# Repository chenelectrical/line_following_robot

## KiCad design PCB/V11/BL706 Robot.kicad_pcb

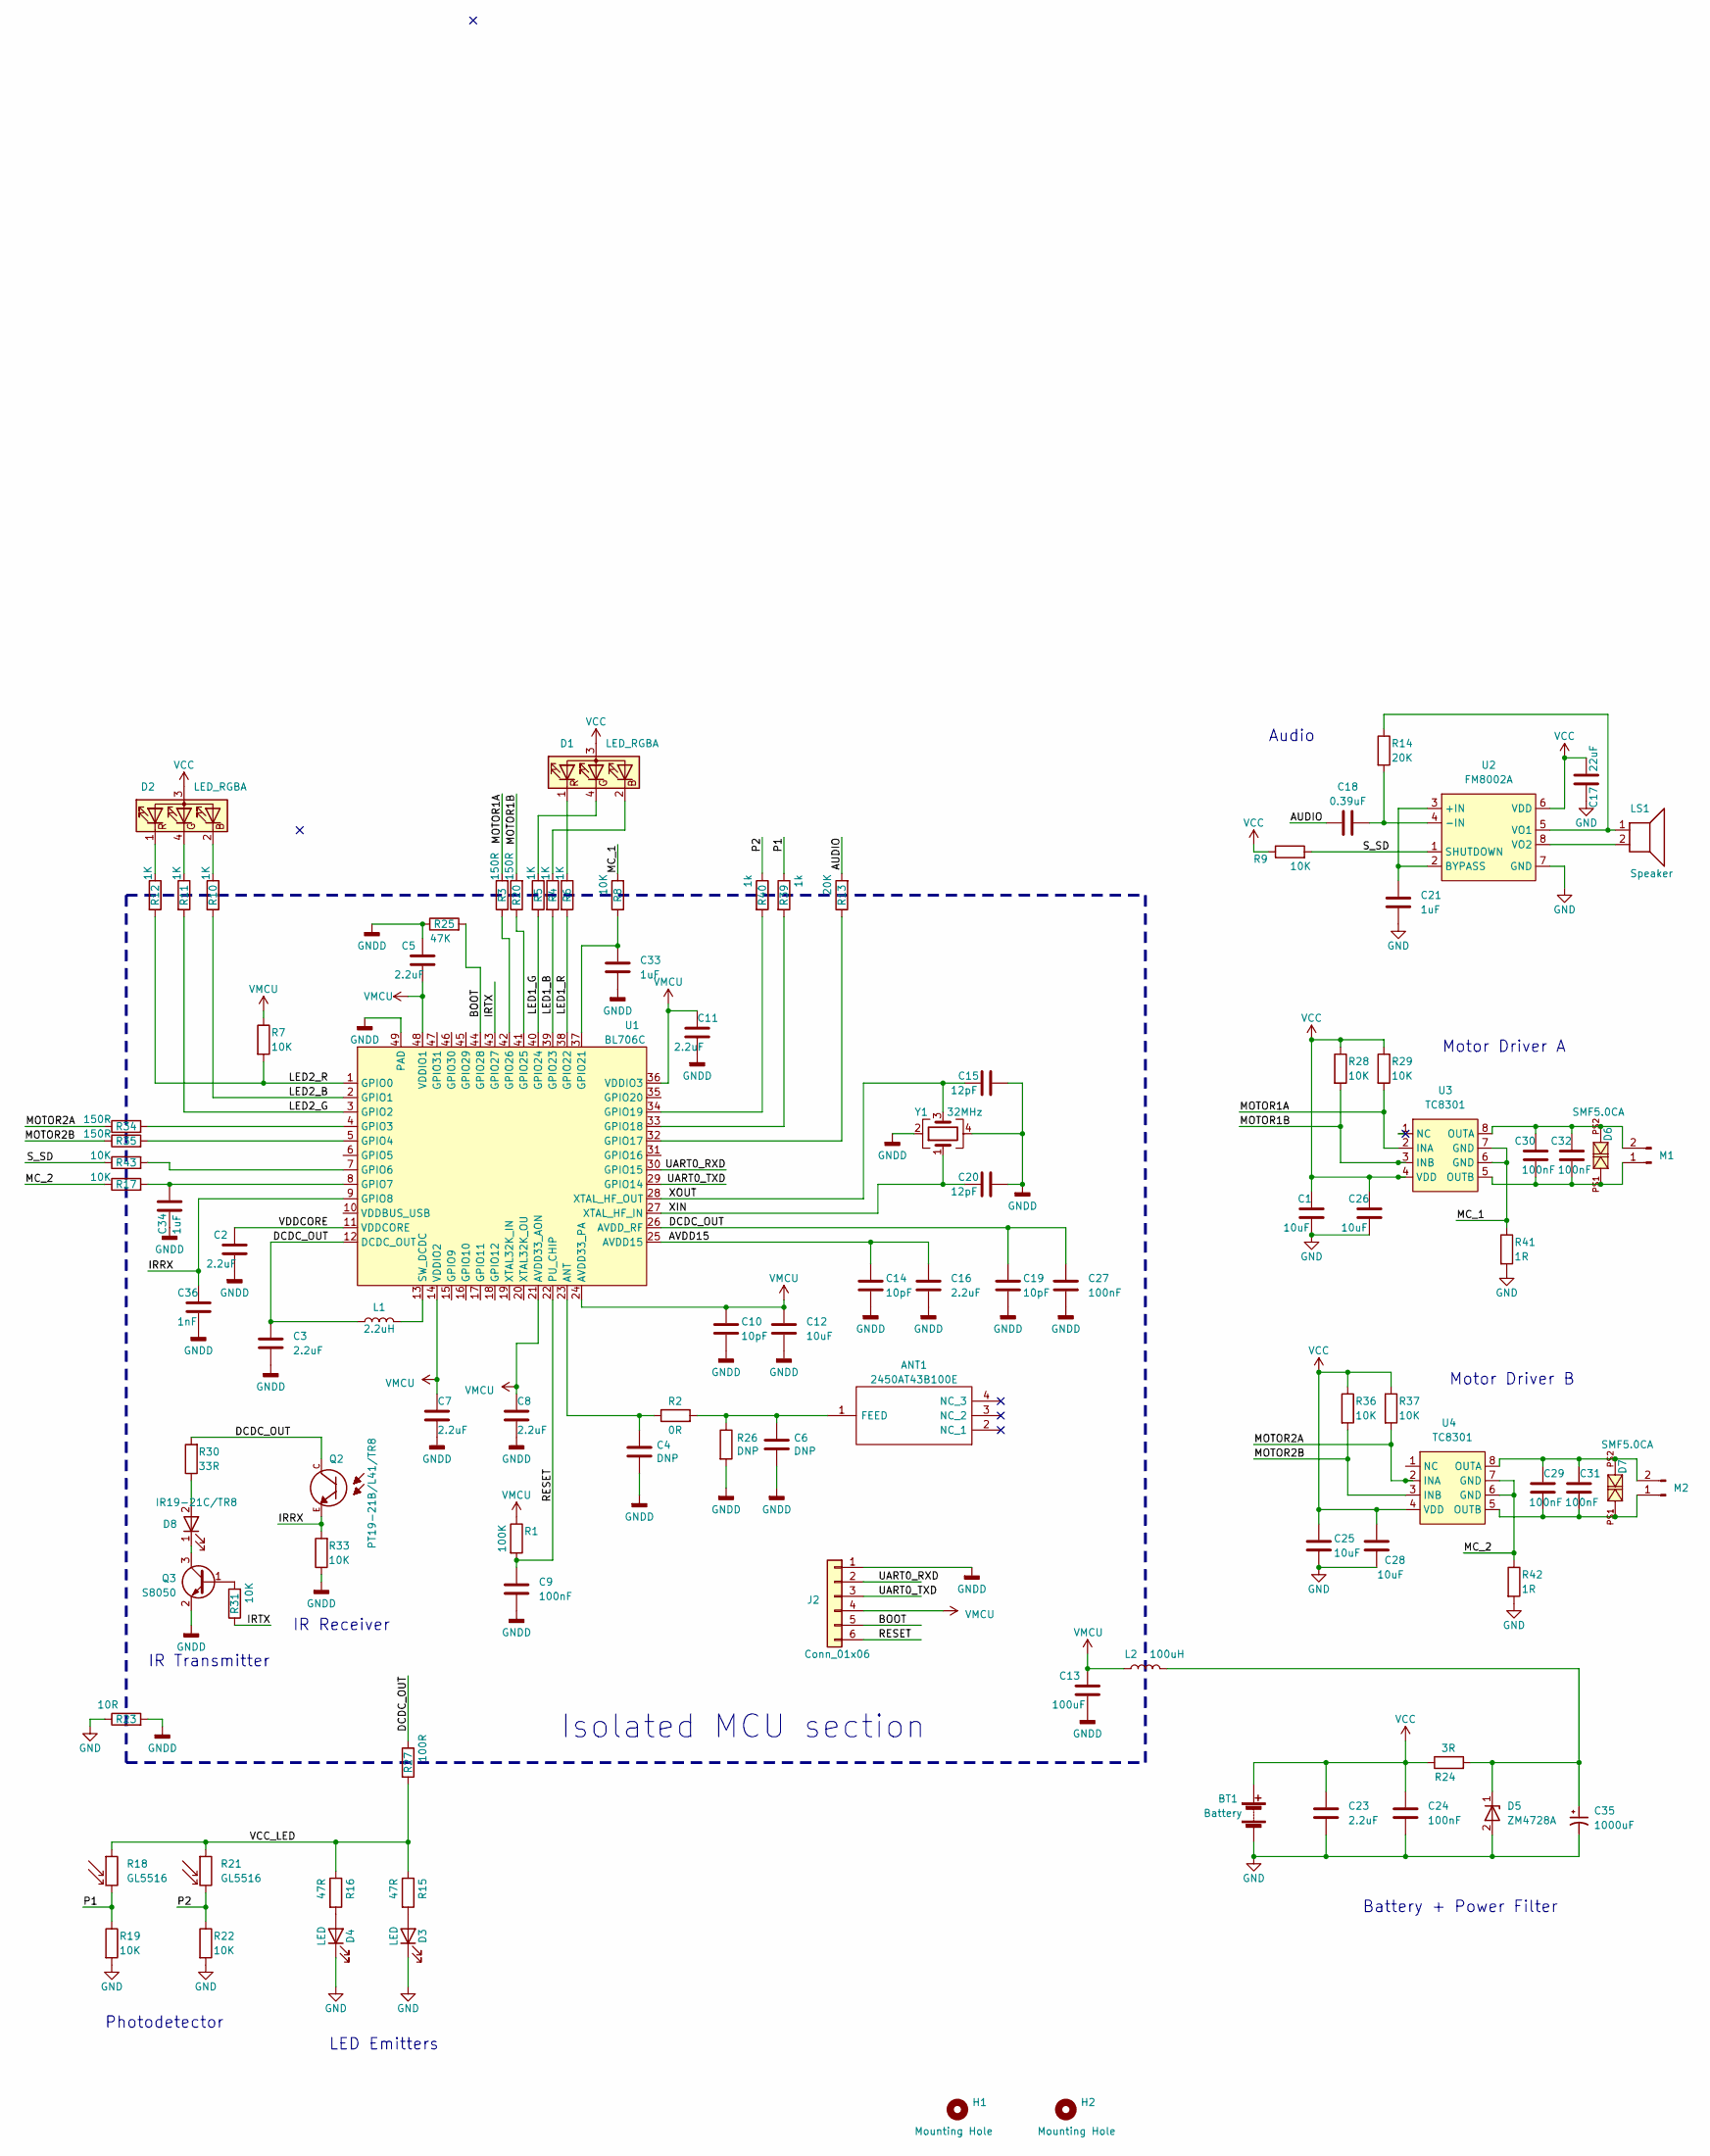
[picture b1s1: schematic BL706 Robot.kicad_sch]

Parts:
ANT1: 2450AT43B100E; LCSC C2917721
BT1: Battery; JST_PH_B2B-PH-K_1x02_P2.00mm_Vertical; LCSC C131337
C1, C12, C25, C26, C28: 10uF; C_0603_1608Metric; LCSC C96446
C2, C3, C5, C7, C8, C11, C16, C23: 2.2uF; C_0402_1005Metric; LCSC C12530
C4, C6: DNP; C_0402_1005Metric
C9, C24, C27, C29, C30, C31, C32: 100nF; C_0402_1005Metric; LCSC C307331
C10, C14, C19: 10pF; C_0402_1005Metric; LCSC C32949
C13: 100uF; CP_EIA-3528-21_Kemet-B; LCSC C129567
C15, C20: 12pF; C_0402_1005Metric; LCSC C1547
C17: 22uF; C_0603_1608Metric; LCSC C162690
C18: 0.39uF; C_0603_1608Metric; LCSC C309480
C21: 1uF; C_0603_1608Metric; LCSC C105504
C33, C34: 1uF; C_0402_1005Metric; LCSC C52923
C35: 1000uF; CP_Elec_8x10.5; LCSC C99833
C36: 1nF; C_0402_1005Metric; LCSC C141053
D1, D2: LED_RGBA; FM-B2020RGBA-HG; LCSC C108793
D3, D4: LED; LED_D3.0mm_Horizontal_O1.27mm_Z2.0mm
D5: ZM4728A; D_MELF; LCSC C38989
D6, D7: SMF5.0CA; SOD-123FL; LCSC C320548
D8: IR19-21C/TR8; IR19-21C-TR8; LCSC C142316
H1, H2: Mounting Hole; MountingHole_3mm
J2: Conn_01x06; PinHeader_1x06_P1.27mm_Vertical
L1: 2.2uH; L_0805_2012Metric; LCSC C86089
L2: 100uH; L_0805_2012Metric; LCSC C223180
LS1: Speaker; JST_XH_B2B-XH-A_1x02_P2.50mm_Vertical; LCSC C158012
M1, M2: Conn_01x02_Male; JST_XH_B2B-XH-A_1x02_P2.50mm_Vertical; LCSC C158012
Q2: PT19-21B/L41/TR8; XDCR_PT19-21B_L41_TR8; LCSC C131258
Q3: S8050; SOT-23-3; LCSC C2926165
R1: 100K; R_0402_1005Metric; LCSC C208776
R2: 0R; R_0402_1005Metric; LCSC C102745
R3, R20, R34, R35: 150R; R_0402_1005Metric; LCSC C140202
R4, R5, R6, R10, R11, R12: 1K; R_0402_1005Metric; LCSC C11702
R7, R8, R9, R17, R19, R22, R28, R29, R31, R33, R43: 10K; R_0402_1005Metric; LCSC C25744
R13, R14: 20K; R_0402_1005Metric; LCSC C25765
R15, R16: 47R; R_0402_1005Metric; LCSC C284589
R18, R21: GL5516; R_LDR_5.0x4.1mm_P3mm_Vertical
R23: 10R; R_1206_3216Metric; LCSC C326706
R24: 3R; R_1206_3216Metric; LCSC C3152278
R25: 47K; R_0402_1005Metric; LCSC C163830
R26: DNP; R_0402_1005Metric
R27: 100R; R_0805_2012Metric; LCSC C2907218
R30: 33R; R_0402_1005Metric; LCSC C208868
R36, R37: 10K; R_0402_1005Metric; LCSC PN C25744
R39, R40: 1k; R_0402_1005Metric; LCSC C11702
R41, R42: 1R; R_1206_3216Metric; LCSC C17928
U1: BL706C; QFN-48-1EP_6x6mm_P0.4mm_EP4.3x4.3mm; LCSC C2874060
U2: FM8002A; SOP-8_3.9x4.9mm_P1.27mm; LCSC C94625
U3, U4: TC8301; SOP-8_3.9x4.9mm_P1.27mm; LCSC C2887481
Y1: 32MHz; Crystal_SMD_2016-4Pin_2.0x1.6mm; LCSC C255896

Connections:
/AUDIO: C18.1, R13.2
/AVDD15: C14.1, C16.1, U1.25 (AVDD15)
/BOOT: J2.5, R25.2, U1.44 (GPIO28)
/DCDC_OUT: C3.1, C19.1, C27.1, L1.1, Q2.C, R27.1, R30.2, U1.12 (DCDC_OUT), U1.26 (AVDD_RF)
/IRRX: C36.1, Q2.E, R33.2, U1.9 (GPIO8)
/IRTX: R31.1, U1.43 (GPIO27)
/LED1_B: R4.2, U1.39 (GPIO23)
/LED1_G: R5.2, U1.40 (GPIO24)
/LED1_R: R6.2, U1.38 (GPIO22)
/LED2_B: R10.2, U1.2 (GPIO1)
/LED2_G: R11.2, U1.3 (GPIO2)
/LED2_R: R7.2, R12.2, U1.1 (GPIO0)
/MC_1: R8.2, R41.1, U3.6 (GND), U3.7 (GND)
/MC_2: R17.1, R42.1, U4.6 (GND), U4.7 (GND)
/MOTOR1A: R3.2, R29.2, U3.2 (INA)
/MOTOR1B: R20.2, R28.2, U3.3 (INB)
/MOTOR2A: R34.1, R37.2, U4.2 (INA)
/MOTOR2B: R35.1, R36.2, U4.3 (INB)
/P1: R18.2, R19.1, R39.1
/P2: R21.2, R22.1, R40.1
/RESET: C9.1, J2.6, R1.2, U1.22 (PU_CHIP)
/S_SD: R9.2, R43.1, U2.1 (SHUTDOWN)
/UART0_RXD: J2.2, U1.30 (GPIO15)
/UART0_TXD: J2.3, U1.29 (GPIO14)
/VCC_LED: R15.1, R16.1, R18.1, R21.1, R27.2
/VDDCORE: C2.1, U1.11 (VDDCORE)
/XIN: C20.2, U1.27 (XTAL_HF_IN), Y1.1
/XOUT: C15.2, U1.28 (XTAL_HF_OUT), Y1.3
GND: BT1.2 (-), C1.2, C17.2, C21.2, C23.2, C24.2, C25.2, C26.2, C28.2, C35.2, D3.1 (K), D4.1 (K), D5.2 (A), R19.2, R22.2, R23.1, R41.2, R42.2, U2.7 (GND)
GNDD: C2.2, C3.2, C4.2, C5.1, C6.2, C7.2, C8.2, C9.2, C10.2, C11.1, C12.2, C13.2, C14.2, C15.1, C16.2, C19.2, C20.1, C27.2, C33.2, C34.2, C36.2, J2.1, Q3.2 (E), R23.2, R25.1, R26.2, R33.1, U1.49 (PAD), Y1.2, Y1.4
unnamed: ANT1.1 (FEED), C6.1, R2.2, R26.1
unnamed: D1.2 (BK), R4.1
unnamed: D1.4 (GK), R5.1
unnamed: D1.1 (RK), R6.1
unnamed: D2.2 (BK), R10.1
unnamed: D2.4 (GK), R11.1
unnamed: D2.1 (RK), R12.1
unnamed: D3.2 (A), R15.2
unnamed: D4.2 (A), R16.2
unnamed: C35.1, D5.1 (K), L2.2, R24.2
unnamed: D8.2 (A), R30.1
unnamed: D8.1 (K), Q3.3 (C)
unnamed: C30.2, C32.2, D6.P$1, M1.1, U3.5 (OUTB)
unnamed: C30.1, C32.1, D6.P$2, M1.2, U3.8 (OUTA)
unnamed: C29.2, C31.2, D7.P$1, M2.1, U4.5 (OUTB)
unnamed: C29.1, C31.1, D7.P$2, M2.2, U4.8 (OUTA)
unnamed: Q3.1 (B), R31.2
unnamed: C4.1, R2.1, U1.23 (ANT)
unnamed: R34.2, U1.4 (GPIO3)
unnamed: R35.2, U1.5 (GPIO4)
unnamed: R43.2, U1.7 (GPIO6)
unnamed: C34.1, R17.2, U1.8 (GPIO7)
unnamed: R13.1, U1.32 (GPIO17)
unnamed: R39.2, U1.33 (GPIO18)
unnamed: R40.2, U1.34 (GPIO19)
unnamed: C33.1, R8.1, U1.37 (GPIO21)
unnamed: R20.1, U1.41 (GPIO25)
unnamed: R3.1, U1.42 (GPIO26)
unnamed: L1.2, U1.13 (SW_DCDC)
unnamed: C21.1, U2.2 (BYPASS), U2.3 (+IN)
unnamed: C18.2, R14.2, U2.4 (-IN)
unnamed: LS1.1, R14.1, U2.5 (VO1)
unnamed: LS1.2, U2.8 (VO2)
VCC: BT1.1 (+), C1.1, C17.1, C23.1, C24.1, C25.1, C26.1, C28.1, D1.3 (A), D2.3 (A), R9.1, R24.1, R28.1, R29.1, R36.1, R37.1, U2.6 (VDD), U3.4 (VDD), U4.4 (VDD)
VPP: C5.2, C7.1, C8.1, C10.1, C11.2, C12.1, C13.1, J2.4, L2.1, R1.1, R7.1, U1.14 (VDDIO2), U1.21 (AVDD33_AON), U1.24 (AVDD33_PA), U1.36 (VDDIO3), U1.48 (VDDIO1)

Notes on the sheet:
Photodetector
Audio
LED Emitters
Motor Driver A
Battery + Power Filter
Isolated MCU section
IR Transmitter
Motor Driver B
IR Receiver

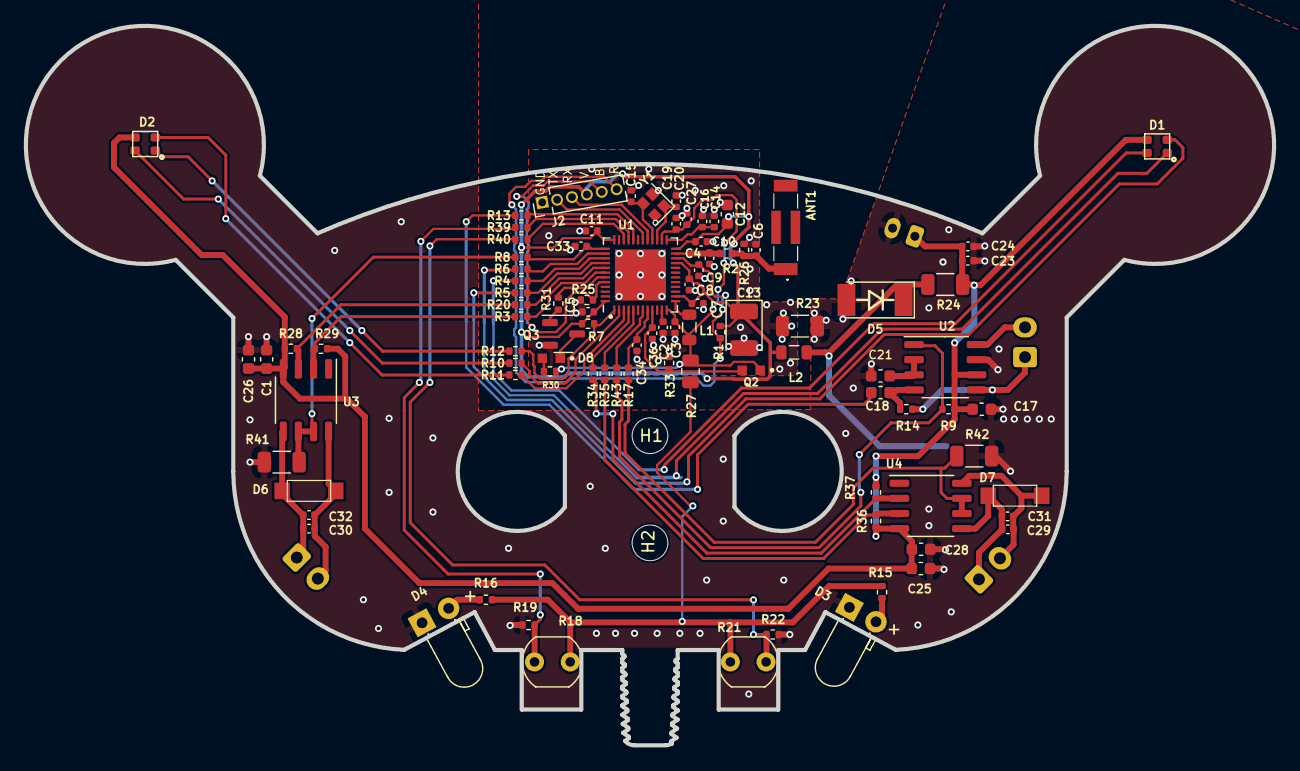
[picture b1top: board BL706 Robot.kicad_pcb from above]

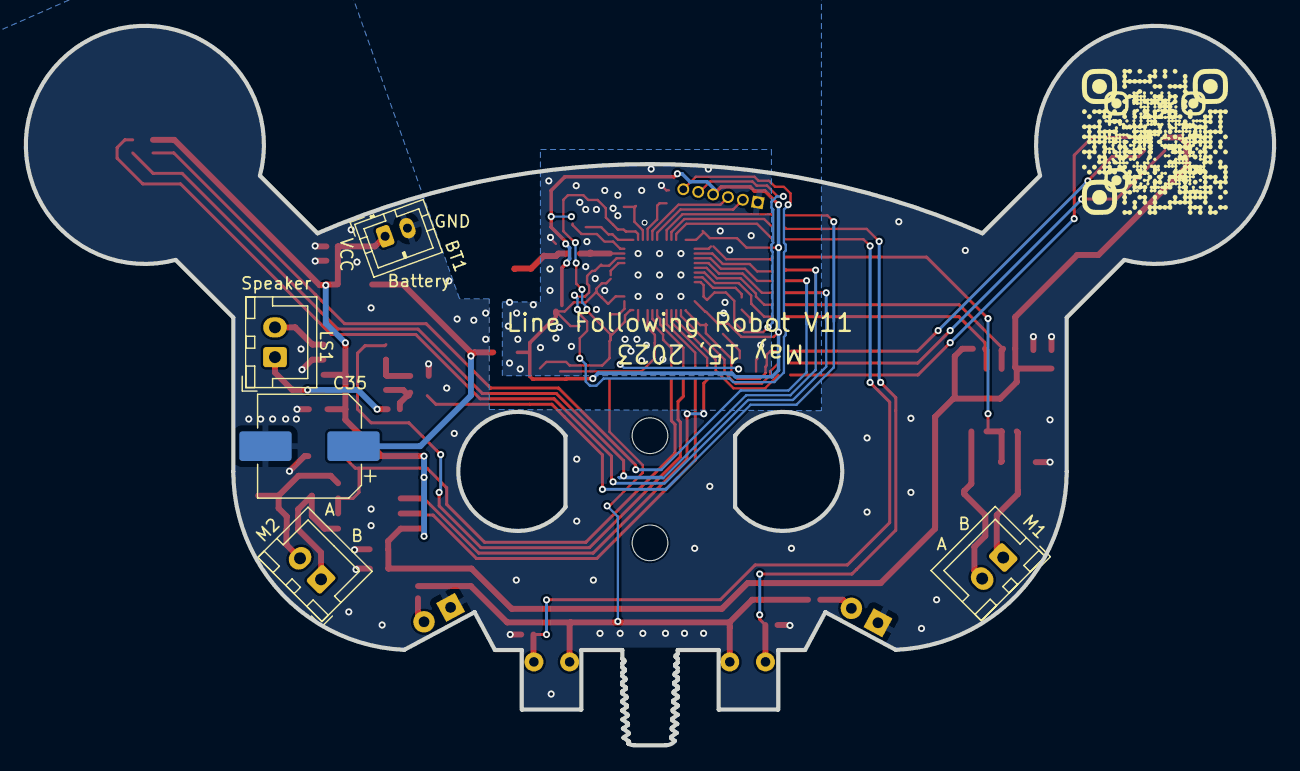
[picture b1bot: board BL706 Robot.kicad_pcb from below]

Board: 2 copper layers, 104.8 x 60.4 mm, 101 parts (5 on the bottom side), 65 nets.

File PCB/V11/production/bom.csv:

Designator,Footprint,Quantity,Value,LCSC Part #
ANT1,2450AT43B100E,1,2450AT43B100E,C2917721
BT1,JST_PH_B2B-PH-K_1x02_P2.00mm_Vertical,1,Battery,C131337
"C1, C12, C25, C26, C28",0603,5,10uF,C96446
"C10, C14, C19",0402,3,10pF,C32949
"C11, C16, C2, C23, C3, C5, C7, C8",0402,8,2.2uF,C12530
C13,CP_EIA-3528-21_Kemet-B,1,100uF,C129567
"C15, C20",0402,2,12pF,C1547
C17,0603,1,22uF,C162690
C18,0603,1,0.39uF,C309480
C21,0603,1,1uF,C105504
"C24, C27, C29, C30, C31, C32, C9",0402,7,100nF,C307331
"C33, C34",0402,2,1uF,C52923
C35,CP_Elec_8x10.5,1,1000uF,C99833
C36,0402,1,1nF,C141053
"C4, C6, R26",0402,3,DNP,
"D1, D2",FM-B2020RGBA-HG,2,LED_RGBA,C108793
"D3, D4",LED_D3.0mm_Horizontal_O1.27mm_Z2.0mm,2,LED,
D5,D_MELF,1,ZM4728A,C38989
"D6, D7",SOD-123FL,2,SMF5.0CA,C320548
D8,IR19-21C-TR8,1,IR19-21C/TR8,C142316
"H1, H2",MountingHole_3mm,2,Mounting Hole,
J2,PinHeader_1x06_P1.27mm_Vertical,1,Conn_01x06,
L1,0805,1,2.2uH,C86089
L2,0805,1,100uH,C223180
LS1,JST_XH_B2B-XH-A_1x02_P2.50mm_Vertical,1,Speaker,C158012
"M1, M2",JST_XH_B2B-XH-A_1x02_P2.50mm_Vertical,2,Conn_01x02_Male,C158012
Q2,XDCR_PT19-21B_L41_TR8,1,PT19-21B/L41/TR8,C131258
Q3,SOT-23-3,1,S8050,C2926165
R1,0402,1,100K,C208776
"R10, R11, R12, R39, R4, R40, R5, R6",0402,8,1K,C11702
"R13, R14",0402,2,20K,C25765
"R15, R16",0402,2,47R,C284589
"R17, R19, R22, R28, R29, R31, R33, R36, R37, R43, R7, R8, R9",0402,13,10K,C25744
"R18, R21",R_LDR_5.0x4.1mm_P3mm_Vertical,2,GL5516,
R2,0402,1,0R,C102745
"R20, R3, R34, R35",0402,4,150R,C140202
R23,1206,1,10R,C326706
R24,1206,1,3R,C3152278
R25,0402,1,47K,C163830
R27,0805,1,100R,C2907218
R30,0402,1,33R,C208868
"R41, R42",1206,2,1R,C17928
U1,QFN-48-1EP_6x6mm_P0.4mm_EP4.3x4.3mm,1,BL706C,C2874060
U2,SOP-8_3.9x4.9mm_P1.27mm,1,FM8002A,C94625
"U3, U4",SOP-8_3.9x4.9mm_P1.27mm,2,TC8301,C2887481
Y1,Crystal_SMD_2016-4Pin_2.0x1.6mm,1,32MHz,C255896

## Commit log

2023-05-15 Create sym-lib-table
2023-05-15 Create fp-lib-table
2023-05-15 Create fp-info-cache
